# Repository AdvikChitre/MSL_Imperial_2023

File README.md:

# MSL_Imperial_2023
Repository for Imperial College London Robocup MSL team 2023

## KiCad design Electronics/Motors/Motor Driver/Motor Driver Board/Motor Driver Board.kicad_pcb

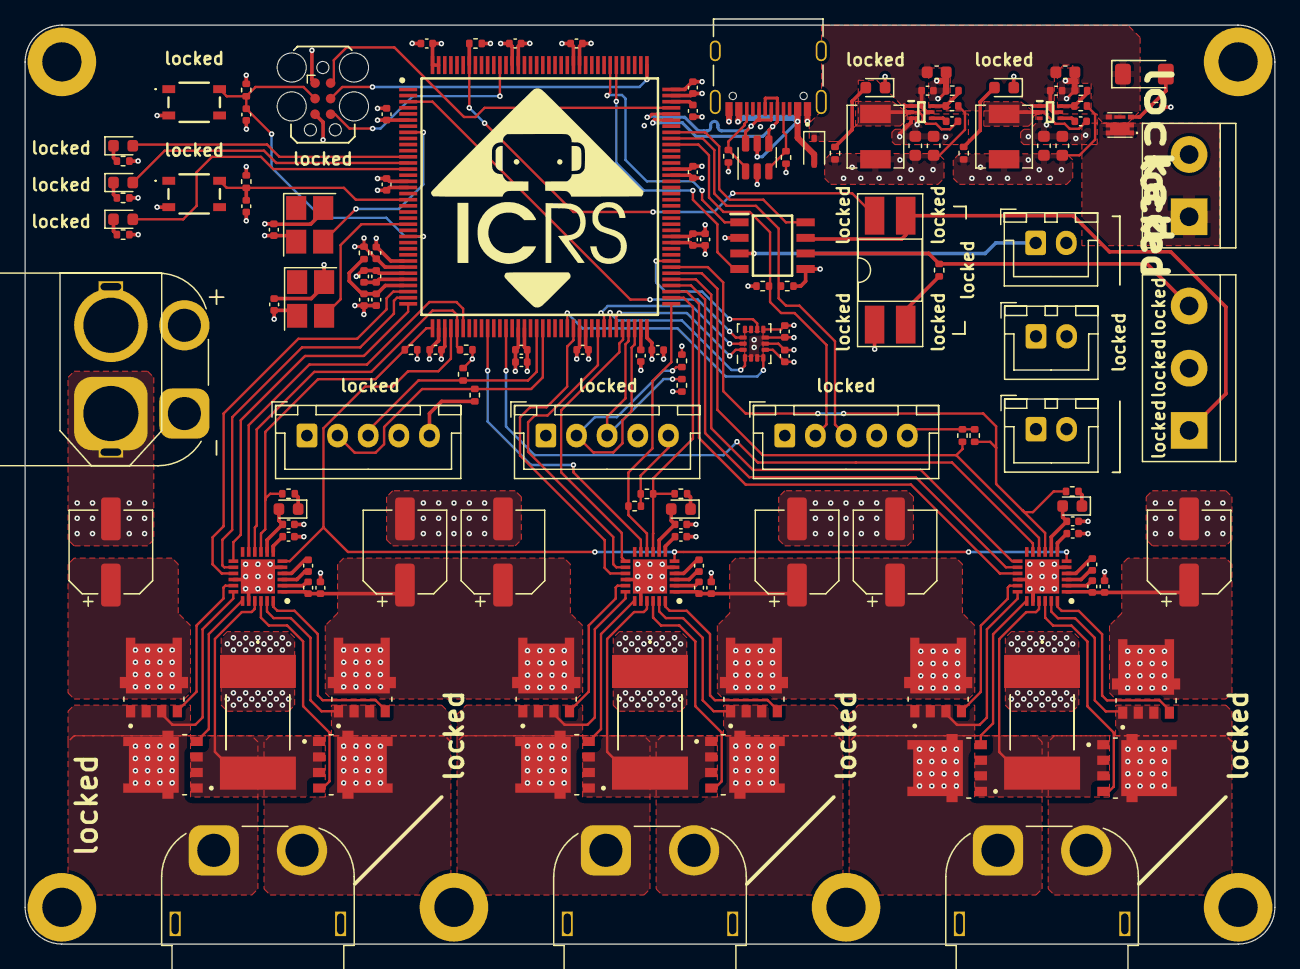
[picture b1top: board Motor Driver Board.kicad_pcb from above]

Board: 4 copper layers, 102.0 x 75.0 mm, 153 parts (0 on the bottom side), 114 nets.

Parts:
C201, C202, C207, C208, C209, C210: 22u; C_0603_1608Metric
C203, C204, C205, C206, C301, C302, C304, C306, C308, C309, C310, C312, C313, C314, C315, C317, C318, C319, C320, C322, C323, C326, C327, C405, C406, C411, C412, C415, C418: 100n; C_0402_1005Metric
C303, C328: 10n; C_0402_1005Metric
C307, C311, C401, C402, C403, C404, C407, C408, C413, C414, C416: 1u; C_0402_1005Metric
C316, C324: 10u; C_0402_1005Metric
C321, C325: 2u2; C_0402_1005Metric
C409, C410, C417, C419, C420, C421: 100u; CP_Elec_6.3x7.7
D201: ZMM10V; D_MiniMELF
D202, D203: GREEN; LED_0603_1608Metric
D301, D401, D402, D403: Red; LED_0603_1608Metric
D302: Green; LED_0603_1608Metric
D303: Blue; LED_0603_1608Metric
D304: BAT760-115; D_SOD-323
FB301: 120R@100MHz; R_0402_1005Metric
H101, H102, H103, H104, H105, H106: MountingHole_Pad; MountingHole_3.2mm_M3_DIN965_Pad
IC201, IC202: TPS563202DRLR; SOTFL50P160X60-6N
IC301: TJA1057GT/3; SOIC127P600X175-8N
IC302: STM32H723ZGT6; QFP50P2200X2200X160-144N
J201, J203, J204: JST-XH-2.50mm; JST_XH_B2B-XH-A_1x02_P2.50mm_Vertical
J202: Pluggable_Terminal_01x02; Pluggable_terminal-2_P5.08mm
J301: TC2030; Tag-Connect_TC2030-IDC-FP_2x03_P1.27mm_Vertical
J302: Pluggable_Terminal_01x03; Pluggable_terminal-3_P5.08mm
J303: TYPE-C-31-M-12; HRO_TYPE-C-31-M-12
J401, J402, J404: XT60PW-F; AMASS_XT60PW-F_1x02_P7.20mm_Horizontal
J403: XT60PW-M; AMASS_XT60PW-M_1x02_P7.20mm_Horizontal
J405: XT60-M-Vertical; AMASS_XT60-M_1x02_P7.20mm_Vertical
J406, J407, J409: JST_2.5mm_1x5; JST_XH_B5B-XH-A_1x05_P2.50mm_Vertical
L201: 4u7; L_Chilisin_BMRA00040420
L202: 3u3; L_Chilisin_BMRA00040420
Q201: DMP3028LFDE; DMP2066UFDE7
R201: 4k7; R_0402_1005Metric
R202: 52k; R_0402_1005Metric
R203, R205, R304, R308, R317, R403, R404, R405, R406, R410, R411: 10k; R_0402_1005Metric
R204: 31k; R_0402_1005Metric
R206, R311, R312, R313, R314, R315, R316: 2k2; R_0402_1005Metric
R207, R301, R302, R303, R401, R402, R409: 1k5; R_0402_1005Metric
R307: 120R; R_0402_1005Metric
R309, R310: 5k1; R_0402_1005Metric
R407, R408, R412: CSS2H-3920K-5L00F; CSS2H3920K5L00F
S301, S304: TS20-42-25-WT-160-SMT-TR; TS204225WT160SMTTRMSL
SW301: SW_DIP_x02; DIP-4_W8.89mm_SMDSocket_LongPads
T401, T402, T403, T404, T405, T406, T407, T408, T409, T410, T411, T412: NVMFS4C05NT1G; TRANS_NVMFS5834NLWFT1G
U302: LSM6DS3; LGA-14_3x2.5mm_P0.5mm_LayoutBorder3x4y
U303: USBLC6-4SC6-ES; SOT-23-6
U401, U402, U403: DRV8701ERGER; QFN50P400X400X100-25N-D
X301: 25MHz_Clock; Oscillator_SMD_Abracon_ASE-4Pin_3.2x2.5mm_HandSoldering
X302: 32.768kHz_Clock; Oscillator_SMD_Abracon_ASE-4Pin_3.2x2.5mm_HandSoldering

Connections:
+3.3V: C208.1, C210.1, C301.1, C302.2, C304.1, C308.1, C310.1, C312.1, C313.1, C314.1, C315.1, C316.1, C317.1, C318.1, C319.1, C320.1, C322.1, C323.1, C324.1, C326.1, C327.1, FB301.2, IC301.5 (VIO), IC302.6 (VBAT), IC302.17 (VDD_1), IC302.30 (VDD_2), IC302.39 (VDD_3), IC302.52 (VDD_4), IC302.62 (VDD_5), IC302.72 (VDD_6), IC302.84 (VDD_7), IC302.95 (VDD33USB), IC302.108 (VDD_8), IC302.121 (VDD_9), IC302.131 (VDD_10), IC302.143 (PDR_ON), IC302.144 (VDD_11), J301.1 (VCC), J406.5, J407.5, J409.5, L202.2, R204.1, R207.1, R304.2, R311.1, R312.1, R313.1, R314.1, R315.1, R316.1, R317.2, R403.1, R404.1, R405.1, R406.1, R410.1, R411.1, SW301.1, U302.5 (VDDIO), U302.8 (VDD), X301.4 (VDD), X302.4 (VDD)
+5V: C207.1, C209.1, IC301.3 (VCC), J201.1, J203.1, J204.1, L201.2, R202.1, R206.1
/Microcontroller/CANH: IC301.7 (CANH), J302.1, SW301.3
/Microcontroller/CANL: IC301.6 (CANL), J302.3, R307.1
/Microcontroller/CAN_SW: R307.2, SW301.2
/Microcontroller/CC1: J303.A5 (CC1), R309.1, U303.3 (IO2)
/Microcontroller/CC2: J303.B5 (CC2), R310.1, U303.1 (IO1)
/Microcontroller/LEDB_K: D303.1 (K), R303.2
/Microcontroller/LEDG_K: D302.1 (K), R302.2
/Microcontroller/LEDR_K: D301.1 (K), R301.2
/Microcontroller/VCAP1: C321.1, IC302.71 (VCAP_1)
/Microcontroller/VCAP2: C325.1, IC302.106 (VCAP_2)
/Microcontroller/VDDA: C309.1, C311.1, FB301.1, IC302.33 (VDDA)
/Microcontroller/VREF+: C306.1, C307.1, IC302.32 (VREF+)
/Motor Drivers/M1_AVDD: C402.1, U402.7 (AVDD)
/Motor Drivers/M1_CPH: C406.2, U402.3 (CPH)
/Motor Drivers/M1_CPL: C406.1, U402.4 (CPL)
/Motor Drivers/M1_DVDD: C404.1, D402.2 (A), U402.8 (DVDD)
/Motor Drivers/M1_GH1: T408.4 (G), U402.17 (GH1)
/Motor Drivers/M1_GH2: T405.4 (G), U402.24 (GH2)
/Motor Drivers/M1_GL1: T407.4 (G), U402.19 (GL1)
/Motor Drivers/M1_GL2: T406.4 (G), U402.22 (GL2)
/Motor Drivers/M1_NFAULT_K: D402.1 (K), R402.2
/Motor Drivers/M1_OUT_A: J402.2 (+), T405.1 (S), T405.2 (S), T405.3 (S), T406.5_6 (D), U402.23 (SH2)
/Motor Drivers/M1_OUT_B: J402.1 (-), T407.5_6 (D), T408.1 (S), T408.2 (S), T408.3 (S), U402.18 (SH1)
/Motor Drivers/M1_SP: R408.2, T406.1 (S), T406.2 (S), T406.3 (S), T407.1 (S), T407.2 (S), T407.3 (S), U402.21 (SP)
/Motor Drivers/M1_VCP: C408.2, U402.2 (VCP)
/Motor Drivers/M2_AVDD: C413.1, U403.7 (AVDD)
/Motor Drivers/M2_CPH: C415.2, U403.3 (CPH)
/Motor Drivers/M2_CPL: C415.1, U403.4 (CPL)
/Motor Drivers/M2_DVDD: C414.1, D403.2 (A), U403.8 (DVDD)
/Motor Drivers/M2_GH1: T412.4 (G), U403.17 (GH1)
/Motor Drivers/M2_GH2: T409.4 (G), U403.24 (GH2)
/Motor Drivers/M2_GL1: T411.4 (G), U403.19 (GL1)
/Motor Drivers/M2_GL2: T410.4 (G), U403.22 (GL2)
/Motor Drivers/M2_NFAULT_K: D403.1 (K), R409.2
/Motor Drivers/M2_OUT_A: J404.2 (+), T409.1 (S), T409.2 (S), T409.3 (S), T410.5_6 (D), U403.23 (SH2)
/Motor Drivers/M2_OUT_B: J404.1 (-), T411.5_6 (D), T412.1 (S), T412.2 (S), T412.3 (S), U403.18 (SH1)
/Motor Drivers/M2_SP: R412.2, T410.1 (S), T410.2 (S), T410.3 (S), T411.1 (S), T411.2 (S), T411.3 (S), U403.21 (SP)
/Motor Drivers/M2_VCP: C416.2, U403.2 (VCP)
/Motor Drivers/M3_AVDD: C401.1, U401.7 (AVDD)
/Motor Drivers/M3_CPH: C405.2, U401.3 (CPH)
/Motor Drivers/M3_CPL: C405.1, U401.4 (CPL)
/Motor Drivers/M3_DVDD: C403.1, D401.2 (A), U401.8 (DVDD)
/Motor Drivers/M3_GH1: T404.4 (G), U401.17 (GH1)
/Motor Drivers/M3_GH2: T401.4 (G), U401.24 (GH2)
/Motor Drivers/M3_GL1: T403.4 (G), U401.19 (GL1)
/Motor Drivers/M3_GL2: T402.4 (G), U401.22 (GL2)
/Motor Drivers/M3_NFAULT_K: D401.1 (K), R401.2
/Motor Drivers/M3_OUT_A: J401.2 (+), T401.1 (S), T401.2 (S), T401.3 (S), T402.5_6 (D), U401.23 (SH2)
/Motor Drivers/M3_OUT_B: J401.1 (-), T403.5_6 (D), T404.1 (S), T404.2 (S), T404.3 (S), U401.18 (SH1)
/Motor Drivers/M3_SP: R407.2, T402.1 (S), T402.2 (S), T402.3 (S), T403.1 (S), T403.2 (S), T403.3 (S), U401.21 (SP)
/Motor Drivers/M3_VCP: C407.2, U401.2 (VCP)
/Power/3V3_BST: C206.1, IC202.4 (BST)
/Power/3V3_FB: IC202.6 (FB), R204.2, R205.1
/Power/3V3_LED_A: D203.2 (A), R207.2
/Power/3V3_SW: C206.2, IC202.2 (SW), L202.1
/Power/5V_BST: C205.1, IC201.4 (BST)
/Power/5V_FB: IC201.6 (FB), R202.2, R203.1
/Power/5V_LED_A: D202.2 (A), R206.2
/Power/5V_SW: C205.2, IC201.2 (SW), L201.1
/Power/RP_PMOS_G: D201.2 (A), Q201.3 (G), R201.1
BOOT0: IC302.138 (BOOT0), R308.1, SW301.4
BTN: C303.1, IC302.19 (PF7), R304.1, S301.2 (NO_2)
CAN_RX: IC301.4 (RXD), IC302.114 (PD0)
CAN_TX: IC301.1 (TXD), IC302.115 (PD1)
CS: IC302.3 (PE4), U302.12 (CS)
GND: C201.2, C202.2, C203.2, C204.2, C207.2, C208.2, C209.2, C210.2, C301.2, C302.1, C303.2, C304.2, C306.2, C307.2, C308.2, C309.2, C310.2, C311.2, C312.2, C313.2, C314.2, C315.2, C316.2, C317.2, C318.2, C319.2, C320.2, C321.2, C322.2, C323.2, C324.2, C325.2, C326.2, C327.2, C328.2, C401.2, C402.2, C403.2, C404.2, C409.2, C410.2, C411.2, C412.2, C413.2, C414.2, C417.2, C418.2, C419.2, C420.2, C421.2, D202.1 (K), D203.1 (K), IC201.3 (GND), IC202.3 (GND), IC301.2 (GND), IC302.16 (VSS_1), IC302.29 (PC3_C), IC302.31 (VSSA), IC302.38 (VSS_2), IC302.51 (VSS_3), IC302.61 (VSS_4), IC302.83 (VSS_5), IC302.94 (VSS_6), IC302.107 (VSS_7), IC302.120 (VSS_8), IC302.130 (VSS_9), J201.2, J202.2, J203.2, J204.2, J301.5 (GND), J302.2, J303.A1_B12 (GND), J303.B1_A12 (GND), J403.1 (-), J403.SH1, J405.1 (-), J406.4, J407.4, J409.4, R201.2, R203.2, R205.2, R301.1, R302.1, R303.1, R308.2, R309.2, R310.2, R407.1, R408.1, R412.1, S301.3 (COM_1), S304.3 (COM_1), U302.2 (SDX), U302.3 (SCX), U302.6 (GND), U302.7 (GND), U303.2 (GND), U401.5 (GND_1), U401.16 (GND_2), U401.20 (SN), U401.25 (GND_3), U402.5 (GND_1), U402.16 (GND_2), U402.20 (SN), U402.25 (GND_3), U403.5 (GND_1), U403.16 (GND_2), U403.20 (SN), U403.25 (GND_3), X301.2 (GND), X302.2 (GND)
IMU_INT1: IC302.59 (PE8), U302.4 (INT1)
IMU_INT2: IC302.80 (PD11), U302.9 (INT2)
LEDB: D303.2 (A), IC302.14 (PF4)
LEDG: D302.2 (A), IC302.12 (PF2)
LEDR: D301.2 (A), IC302.13 (PF3)
M1_EN: IC302.35 (PA1), U402.14 (EN)
M1_NFAULT: IC302.37 (PA3), R402.1, R404.2, U402.9 (NFAULT)
M1_NSLEEP: IC302.36 (PA2), U402.13 (NSLEEP)
M1_PH: IC302.34 (PA0), U402.15 (PH)
M1_SNSOUT: IC302.41 (PA5), R406.2, U402.10 (SNSOUT)
M1_SO: IC302.42 (PA6), U402.11 (SO)
M2_EN: IC302.64 (PE11), U403.14 (EN)
M2_NFAULT: IC302.74 (PB13), R409.1, R410.2, U403.9 (NFAULT)
M2_NSLEEP: IC302.68 (PE15), U403.13 (NSLEEP)
M2_PH: IC302.60 (PE9), U403.15 (PH)
M2_SNSOUT: IC302.73 (PB12), R411.2, U403.10 (SNSOUT)
M2_SO: IC302.46 (PB0), U403.11 (SO)
M3_EN: IC302.76 (PB15), U401.14 (EN)
M3_NFAULT: IC302.79 (PD10), R401.1, R403.2, U401.9 (NFAULT)
M3_NSLEEP: IC302.77 (PD8), U401.13 (NSLEEP)
M3_PH: IC302.75 (PB14), U401.15 (PH)
M3_SNSOUT: IC302.78 (PD9), R405.2, U401.10 (SNSOUT)
M3_SO: IC302.49 (PF11), U401.11 (SO)
MISO: IC302.66 (PE13), U302.1 (SDO/SA0)
MOSI: IC302.67 (PE14), U302.14 (SDA)
NRST: C328.1, IC302.25 (NRST), J301.3 (~RESET), R317.1, S304.2 (NO_2)
OSC25M: IC302.23 (PH0-OSC_IN), X301.3 (OUT)
OSC32K: IC302.8 (PC14-OSC32_IN), X302.3 (OUT)
SCK: IC302.65 (PE12), U302.13 (SCL)
SCL2: IC302.69 (PB10), J406.3, R315.2
SCL3: IC302.100 (PA8), J407.3, R311.2
SCL4: IC302.54 (PF14), J409.3, R312.2
SDA2: IC302.70 (PB11), J406.2, R316.2
SDA3: IC302.99 (PC9), J407.2, R313.2
SDA4: IC302.55 (PF15), J409.2, R314.2
SILENT: IC301.8 (S), IC302.101 (PA9)
SWCLK: IC302.109 (PA14), J301.4 (SWCLK)
SWDIO: IC302.105 (PA13), J301.2 (SWDIO)
SWO: IC302.133 (PB3), J301.6 (SWO)
USB_DN: IC302.103 (PA11), J303.A7 (DN1), J303.B7 (DN2), U303.4 (IO3)
USB_DP: IC302.104 (PA12), J303.A6 (DP1), J303.B6 (DP2), U303.6 (IO4)
VBUS: D304.2 (A), J303.A4_B9 (VBUS), J303.B4_A9 (VBUS), U303.5 (VBUS)
VIN: C201.1, C202.1, C203.1, C204.1, D201.1 (K), D304.1 (K), IC201.1 (VIN), IC201.5 (EN), IC202.1 (VIN), IC202.5 (EN), Q201.4 (S_1), Q201.7 (S_2)
VIN_RAW: J202.1, Q201.1 (D_1), Q201.2 (D_2), Q201.5 (D_3), Q201.6 (D_4), Q201.8 (D_5)
VMOT: C407.1, C408.1, C409.1, C410.1, C411.1, C412.1, C416.1, C417.1, C418.1, C419.1, C420.1, C421.1, J403.2 (+), J403.SH2, J405.2 (+), T401.5_6 (D), T404.5_6 (D), T405.5_6 (D), T408.5_6 (D), T409.5_6 (D), T412.5_6 (D), U401.1 (VM), U402.1 (VM), U403.1 (VM)
VREF: IC302.40 (PA4), U401.6 (VREF), U402.6 (VREF), U403.6 (VREF)

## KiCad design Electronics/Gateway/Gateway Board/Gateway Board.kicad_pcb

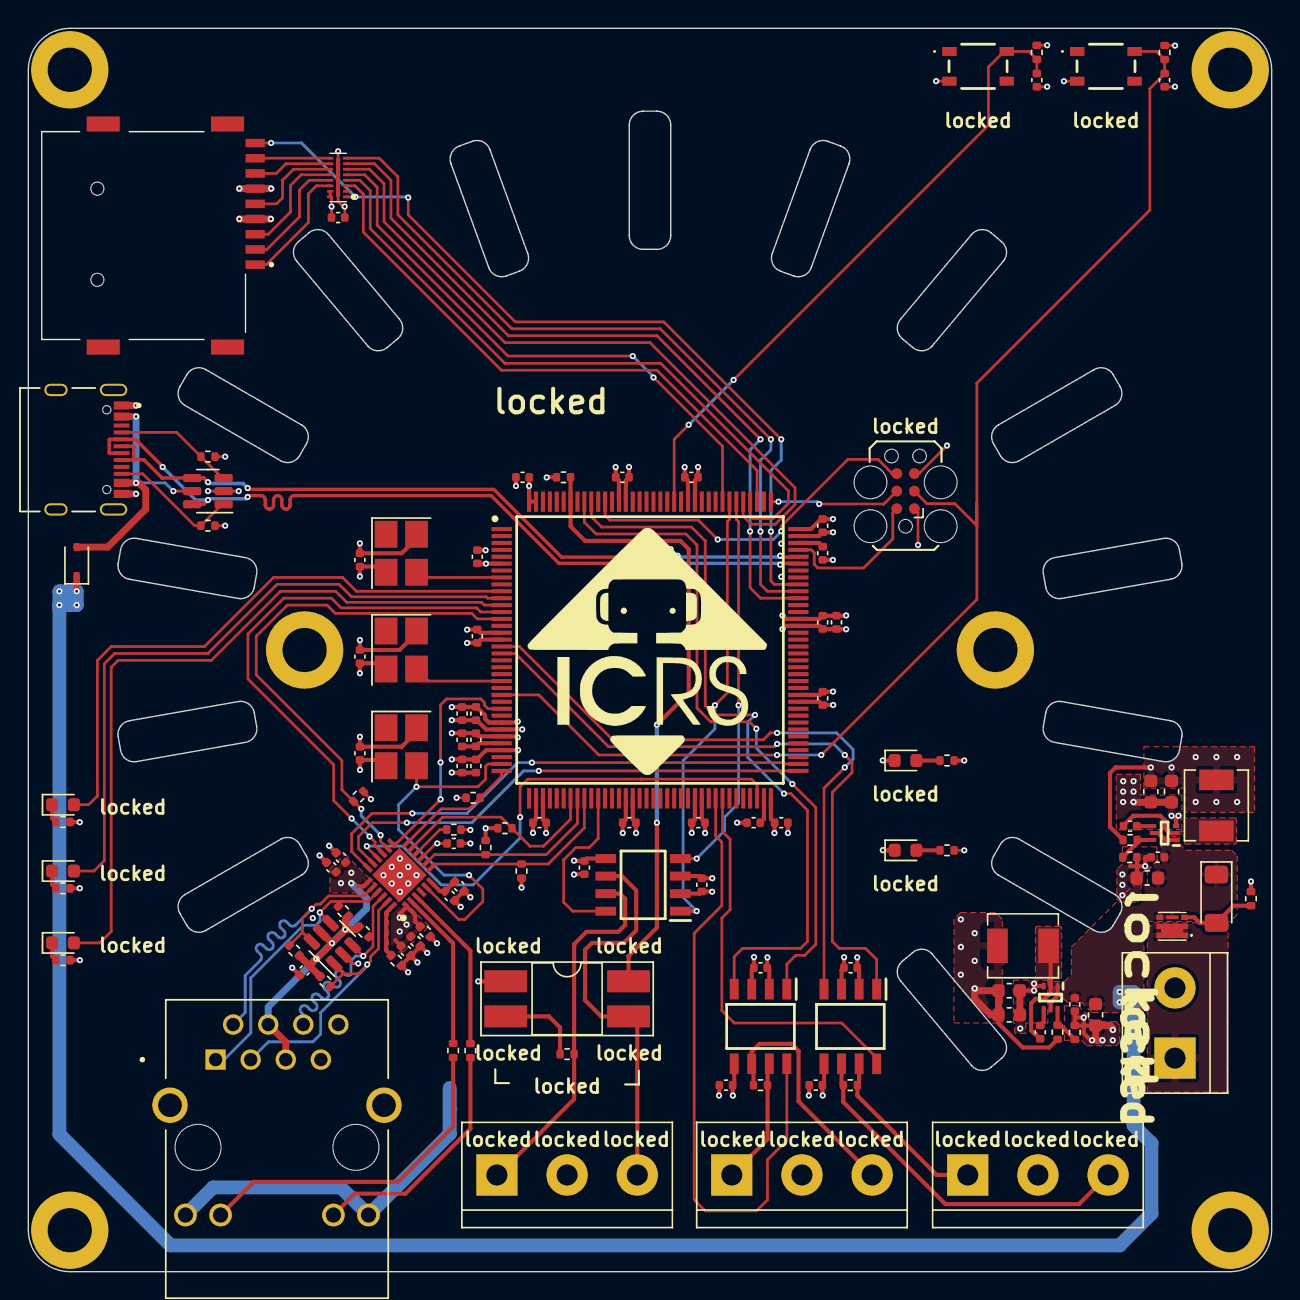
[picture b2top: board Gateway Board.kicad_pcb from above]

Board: 4 copper layers, 90.0 x 90.0 mm, 123 parts (0 on the bottom side), 88 nets.

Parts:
C1, C2, C3, C4, C5, C6, C203, C204, C205, C206, C301, C302, C303, C305, C307, C308, C309, C311, C312, C313, C314, C316, C317, C318, C319, C320, C321, C327, C401, C404, C405, C406, C408: 100n; C_0402_1005Metric
C201, C202, C207, C208, C209, C210: 22u; C_0603_1608Metric
C304, C326: 10n; C_0402_1005Metric
C306, C310, C402: 1u; C_0402_1005Metric
C315, C322, C325, C407: 10u; C_0402_1005Metric
C323, C324: 2u2; C_0402_1005Metric
C403: 470p; C_0402_1005Metric
D201, D202: GREEN; LED_0603_1608Metric
D204: ZMM10V; D_MiniMELF
D301: Red; LED_0603_1608Metric
D302: Green; LED_0603_1608Metric
D303: Blue; LED_0603_1608Metric
D304: BAT760-115; D_SOD-323
FB401: 120R@100MHz; R_0402_1005Metric
FL301: EMIF06-MSD02N16; EMIF06MSD02N16
H101, H102, H103, H104, H105, H106: MountingHole_Pad; MountingHole_3.2mm_M3_DIN965_Pad
IC201, IC202: TPS563202DRLR; SOTFL50P160X60-6N
IC301: STM32H723ZGT6; QFP50P2200X2200X160-144N
IC302, IC303, IC304: TJA1057GT/3; SOIC127P600X175-8N
IC401: LAN8742A-CZ-TR; QFN50P400X400X100-25N-D
J201: Pluggable_Terminal_01x02; Pluggable_terminal-2_P5.08mm
J301: TC2030; Tag-Connect_TC2030-IDC-FP_2x03_P1.27mm_Vertical
J302: MEM2075-00-140-01-A; MEM20750014001A
J303: TYPE-C-31-M-12; HRO_TYPE-C-31-M-12
J304, J305, J306: Pluggable_Terminal_01x03; Pluggable_terminal-3_P5.08mm
J401: HR913129A; HANRUN_HR913129A
L201: 4u7; L_Chilisin_BMRA00040420
L202: 3u3; L_Chilisin_BMRA00040420
Q201: DMP3028LFDE; DMP2066UFDE7
R201: 52k; R_0402_1005Metric
R202, R204, R305, R306, R311, R401, R402, R403, R404, R406: 10k; R_0402_1005Metric
R203: 31k; R_0402_1005Metric
R205: 2k2; R_0402_1005Metric
R206, R301, R303, R304, R405: 1k5; R_0402_1005Metric
R207: 4k7; R_0402_1005Metric
R302, R307, R310: 120R; R_0402_1005Metric
R308, R309: 5k1; R_0402_1005Metric
R407: 12k1; R_0402_1005Metric
R408, R409, R410, R411: 49R9; R_0402_1005Metric
R412, R413: 330R; R_0402_1005Metric
S301, S302: TS20-42-25-WT-160-SMT-TR; TS204225WT160SMTTRMSL
SW301: SW_DIP_x02; DIP-4_W8.89mm_SMDSocket_LongPads
U302, U401: USBLC6-4SC6-ES; SOT-23-6
X301: 50MHz_Clock; Oscillator_SMD_Abracon_ASE-4Pin_3.2x2.5mm_HandSoldering
X302: 25MHz_Clock; Oscillator_SMD_Abracon_ASE-4Pin_3.2x2.5mm_HandSoldering
X303: 32.768kHz_Clock; Oscillator_SMD_Abracon_ASE-4Pin_3.2x2.5mm_HandSoldering

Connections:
+3.3V: C1.1, C3.1, C5.1, C208.1, C210.1, C301.2, C302.2, C303.2, C307.1, C308.1, C309.1, C310.1, C311.1, C312.1, C313.1, C314.1, C315.1, C316.1, C317.1, C318.1, C319.1, C320.1, C321.1, C322.1, C325.1, C327.1, C401.2, FB401.2, FL301.15 (VCC), FL301.16 (RDATA_VCC), IC301.6 (VBAT), IC301.17 (VDD_1), IC301.30 (VDD_2), IC301.33 (VDDA), IC301.39 (VDD_3), IC301.52 (VDD_4), IC301.62 (VDD_5), IC301.72 (VDD_6), IC301.84 (VDD_7), IC301.95 (VDD33USB), IC301.108 (VDD_8), IC301.121 (VDD_9), IC301.131 (VDD_10), IC301.143 (PDR_ON), IC301.144 (VDD_11), IC302.5 (VIO), IC303.5 (VIO), IC304.5 (VIO), IC401.9 (VDDIO), J301.1 (VCC), J302.4 (VDD), J401.9, J401.12, L202.2, R203.1, R206.1, R305.2, R311.2, R402.1, R403.1, R404.1, R405.1, R406.1, SW301.1, X301.4 (VDD), X302.4 (VDD), X303.4 (VDD)
+3.3VA: C404.1, C405.1, C406.1, C407.1, C408.1, FB401.1, IC401.1 (VDD2A), IC401.19 (VDD1A), J401.4 (TCT), J401.5 (RCT), R408.1, R409.1, R410.1, R411.1, U401.5 (VBUS)
+5V: C2.1, C4.1, C6.1, C207.1, C209.1, IC302.3 (VCC), IC303.3 (VCC), IC304.3 (VCC), L201.2, R201.1, R205.1
/Ethernet/G_K: J401.10, R412.2
/Ethernet/LED1: IC401.3 (LED1/REGOFF), R413.1
/Ethernet/LED2: IC401.2 (LED2/~INTSEL), R412.1
/Ethernet/PHYAD0: IC401.10 (RXER/PHYAD0), R401.1
/Ethernet/RBIAS: IC401.24 (RBIAS), R407.1
/Ethernet/RXN: IC401.22 (RXN), J401.6 (RD-), R411.2, U401.3 (IO2)
/Ethernet/RXP: IC401.23 (RXP), J401.3 (RD+), R410.2, U401.1 (IO1)
/Ethernet/TXN: IC401.20 (TXN), J401.2 (TD-), R409.2, U401.6 (IO4)
/Ethernet/TXP: IC401.21 (TXP), J401.1 (TD+), R408.2, U401.4 (IO3)
/Ethernet/VDDCR: C402.1, C403.1, IC401.6 (VDDCR)
/Ethernet/Y_K: J401.11, R413.2
/Microcontroller/CANH1: IC302.7 (CANH), J304.1, R302.1
/Microcontroller/CANH2: IC303.7 (CANH), J305.1, R307.2
/Microcontroller/CANH3: IC304.7 (CANH), J306.1, R310.2
/Microcontroller/CANL1: IC302.6 (CANL), J304.3, SW301.3
/Microcontroller/CANL2: IC303.6 (CANL), J305.3, R307.1
/Microcontroller/CANL3: IC304.6 (CANL), J306.3, R310.1
/Microcontroller/CAN_SW: R302.2, SW301.2
/Microcontroller/CC1: J303.A5 (CC1), R308.1, U302.3 (IO2)
/Microcontroller/CC2: J303.B5 (CC2), R309.1, U302.1 (IO1)
/Microcontroller/CLK: FL301.11 (CLK_EX), J302.5 (CLK)
/Microcontroller/CMD: FL301.12 (CMD_EX), J302.3 (CMD)
/Microcontroller/DAT0: FL301.10 (DAT0_EX), J302.7 (DAT0)
/Microcontroller/DAT1: FL301.9 (DAT1_EX), J302.8 (DAT1)
/Microcontroller/DAT2: FL301.14 (DAT2_EX), J302.1 (DAT2)
/Microcontroller/DAT3: FL301.13 (DAT3_EX), J302.2 (CD/DAT3)
/Microcontroller/LEDB_K: D303.1 (K), R304.2
/Microcontroller/LEDG_K: D302.1 (K), R303.2
/Microcontroller/LEDR_K: D301.1 (K), R301.2
/Microcontroller/VCAP1: C323.1, IC301.71 (VCAP_1)
/Microcontroller/VCAP2: C324.1, IC301.106 (VCAP_2)
/Microcontroller/VREF+: C305.1, C306.1, IC301.32 (VREF+)
/Power/3V3_BST: C206.1, IC202.4 (BST)
/Power/3V3_FB: IC202.6 (FB), R203.2, R204.1
/Power/3V3_LED_A: D202.2 (A), R206.2
/Power/3V3_SW: C206.2, IC202.2 (SW), L202.1
/Power/5V_BST: C205.1, IC201.4 (BST)
/Power/5V_FB: IC201.6 (FB), R201.2, R202.1
/Power/5V_LED_A: D201.2 (A), R205.2
/Power/5V_SW: C205.2, IC201.2 (SW), L201.1
/Power/RP_PMOS_G: D204.2 (A), Q201.3 (G), R207.1
BOOT0: IC301.138 (BOOT0), R306.1, SW301.4
BTN: C326.1, IC301.123 (PD7), R311.1, S302.2 (NO_2)
CAN_RX1: IC301.114 (PD0), IC302.4 (RXD)
CAN_RX2: IC301.135 (PB5), IC303.4 (RXD)
CAN_RX3: IC301.18 (PF6), IC304.4 (RXD)
CAN_TX1: IC301.115 (PD1), IC302.1 (TXD)
CAN_TX2: IC301.136 (PB6), IC303.1 (TXD)
CAN_TX3: IC301.19 (PF7), IC304.1 (TXD)
ETH_CRS_DV: IC301.43 (PA7), IC401.11 (CRS_DV/MODE2), R404.2
ETH_INT: IC301.14 (PF4), IC401.14 (~INT/REFCLKO), R406.2
ETH_MDC: IC301.27 (PC1), IC401.13 (MDC)
ETH_MDIO: IC301.36 (PA2), IC401.12 (MDIO), R405.2
ETH_REF_CLK: IC301.35 (PA1), IC401.5 (XTAL1/CLKIN), X301.3 (OUT)
ETH_RST: IC301.13 (PF3), IC401.15 (~RST)
ETH_RXD0: IC301.44 (PC4), IC401.8 (RXD0/MODE0), R402.2
ETH_RXD1: IC301.45 (PC5), IC401.7 (RXD1/MODE1), R403.2
ETH_TXD0: IC301.73 (PB12), IC401.17 (TXD0)
ETH_TXD1: IC301.74 (PB13), IC401.18 (TXD1)
ETH_TX_EN: IC301.70 (PB11), IC401.16 (TXEN)
GND: C1.2, C2.2, C3.2, C4.2, C5.2, C6.2, C201.2, C202.2, C203.2, C204.2, C207.2, C208.2, C209.2, C210.2, C301.1, C302.1, C303.1, C304.2, C305.2, C306.2, C307.2, C308.2, C309.2, C310.2, C311.2, C312.2, C313.2, C314.2, C315.2, C316.2, C317.2, C318.2, C319.2, C320.2, C321.2, C322.2, C323.2, C324.2, C325.2, C326.2, C327.2, C401.1, C402.2, C403.2, C404.2, C405.2, C406.2, C407.2, C408.2, D201.1 (K), D202.1 (K), FL301.17 (EP_(GND)), IC201.3 (GND), IC202.3 (GND), IC301.16 (VSS_1), IC301.29 (PC3_C), IC301.31 (VSSA), IC301.38 (VSS_2), IC301.51 (VSS_3), IC301.61 (VSS_4), IC301.83 (VSS_5), IC301.94 (VSS_6), IC301.107 (VSS_7), IC301.120 (VSS_8), IC301.130 (VSS_9), IC302.2 (GND), IC303.2 (GND), IC304.2 (GND), IC401.25 (VSS), J201.2, J301.5 (GND), J302.6 (VSS), J303.A1_B12 (GND), J303.B1_A12 (GND), J304.2, J305.2, J306.2, J401.8 (CHS_GND), J401.S1 (SHIELD), J401.S2 (SHIELD), R202.2, R204.2, R207.2, R301.1, R303.1, R304.1, R306.2, R308.2, R309.2, R401.2, R407.2, S301.3 (COM_1), S302.3 (COM_1), U302.2 (GND), U401.2 (GND), X301.2 (GND), X302.2 (GND), X303.2 (GND)
LEDB: D303.2 (A), IC301.12 (PF2)
LEDG: D302.2 (A), IC301.10 (PF0)
LEDR: D301.2 (A), IC301.11 (PF1)
NRST: C304.1, IC301.25 (NRST), J301.3 (~RESET), R305.1, S301.2 (NO_2)
OSC25M: IC301.23 (PH0-OSC_IN), X302.3 (OUT)
OSC32K: IC301.8 (PC14-OSC32_IN), X303.3 (OUT)
SDMMC1_CD: FL301.1 (WP/CD), IC301.100 (PA8), J302.9 (CD)
SDMMC1_CLK: FL301.6 (CLK_IN), IC301.113 (PC12)
SDMMC1_CMD: FL301.5 (CMD_IN), IC301.116 (PD2)
SDMMC1_DAT0: FL301.7 (DAT0_IN), IC301.98 (PC8)
SDMMC1_DAT1: FL301.8 (DAT1_IN), IC301.99 (PC9)
SDMMC1_DAT2: FL301.3 (DAT2_IN), IC301.111 (PC10)
SDMMC1_DAT3: FL301.4 (DAT3_IN), IC301.112 (PC11)
SILENT1: IC301.47 (PB1), IC302.8 (S)
SILENT2: IC301.64 (PE11), IC303.8 (S)
SILENT3: IC301.65 (PE12), IC304.8 (S)
SWCLK: IC301.109 (PA14), J301.4 (SWCLK)
SWDIO: IC301.105 (PA13), J301.2 (SWDIO)
SWO: IC301.133 (PB3), J301.6 (SWO)
USB_DN: IC301.103 (PA11), J303.A7 (DN1), J303.B7 (DN2), U302.6 (IO4)
USB_DP: IC301.104 (PA12), J303.A6 (DP1), J303.B6 (DP2), U302.4 (IO3)
VBUS: D304.2 (A), J303.A4_B9 (VBUS), J303.B4_A9 (VBUS), U302.5 (VBUS)
VIN: C201.1, C202.1, C203.1, C204.1, D204.1 (K), D304.1 (K), IC201.1 (VIN), IC201.5 (EN), IC202.1 (VIN), IC202.5 (EN), Q201.4 (S_1), Q201.7 (S_2)
VIN_RAW: J201.1, Q201.1 (D_1), Q201.2 (D_2), Q201.5 (D_3), Q201.6 (D_4), Q201.8 (D_5)

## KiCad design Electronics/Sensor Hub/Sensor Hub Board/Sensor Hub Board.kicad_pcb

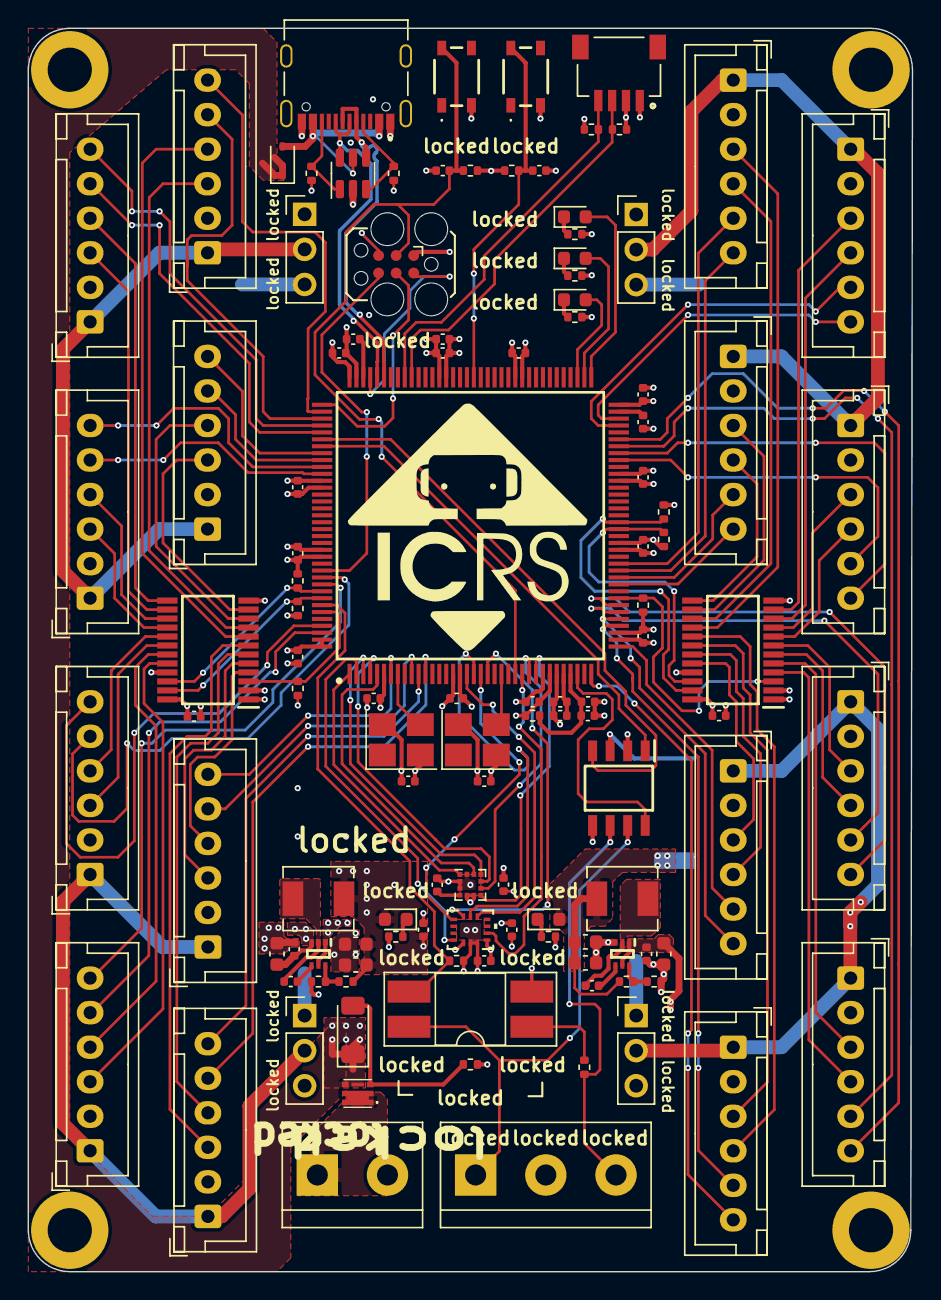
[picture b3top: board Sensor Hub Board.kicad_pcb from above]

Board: 4 copper layers, 64.0 x 90.0 mm, 119 parts (0 on the bottom side), 132 nets.

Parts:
C201, C202, C207, C208, C209, C210: 22u; C_0603_1608Metric
C203, C204, C205, C206, C301, C302, C304, C306, C307, C308, C310, C311, C312, C313, C315, C316, C317, C318, C320, C321, C401, C402, C403, C404, C405, C407: 100n; C_0402_1005Metric
C303, C324: 10n; C_0402_1005Metric
C305, C309, C406: 1u; C_0402_1005Metric
C314, C322: 10u; C_0402_1005Metric
C319, C323: 2u2; C_0402_1005Metric
D201: ZMM10V; D_MiniMELF
D202, D203: GREEN; LED_0603_1608Metric
D301: Red; LED_0603_1608Metric
D302: Green; LED_0603_1608Metric
D303: Blue; LED_0603_1608Metric
D304: BAT760-115; D_SOD-323
FB301: 120R@100MHz; R_0402_1005Metric
H101, H102, H103, H104: MountingHole_Pad; MountingHole_3.2mm_M3_DIN965_Pad
IC201, IC202: TPS563202DRLR; SOTFL50P160X60-6N
IC301: TJA1057GT/3; SOIC127P600X175-8N
IC302: STM32H723ZGT6; QFP50P2200X2200X160-144N
J203: Pluggable_Terminal_01x02; Pluggable_terminal-2_P5.08mm
J301: TC2030; Tag-Connect_TC2030-IDC-FP_2x03_P1.27mm_Vertical
J302: Pluggable_Terminal_01x03; Pluggable_terminal-3_P5.08mm
J303: TYPE-C-31-M-12; HRO_TYPE-C-31-M-12
J304: JST_SH_1mm_1x4
J401, J402, J403, J404, J405, J406, J407, J408, J409, J410, J411, J412, J413, J414, J415, J416: JST_2.5mm_1x6; JST_XH_B6B-XH-A_1x06_P2.50mm_Vertical
JP401, JP402, JP403, JP404: Jumper_3_Bridged12; PinHeader_1x03_P2.54mm_Vertical
L201: 4u7; L_Chilisin_BMRA00040420
L202: 3u3; L_Chilisin_BMRA00040420
Q201: DMP3028LFDE; DMP2066UFDE7
R201: 4k7; R_0402_1005Metric
R202: 52k; R_0402_1005Metric
R203, R205, R304, R306, R313, R401, R402: 10k; R_0402_1005Metric
R204: 31k; R_0402_1005Metric
R206, R309, R310, R311, R312, R314, R315: 2k2; R_0402_1005Metric
R207, R301, R302, R303: 1k5; R_0402_1005Metric
R305: 120R; R_0402_1005Metric
R307, R308: 5k1; R_0402_1005Metric
S301, S302: TS20-42-25-WT-160-SMT-TR; TS204225WT160SMTTRMSL
SW301: SW_DIP_x02; DIP-4_W8.89mm_SMDSocket_LongPads
U302: USBLC6-4SC6-ES; SOT-23-6
U401, U403: TCA9548APWR; SOP65P640X120-24N
U402: BMI270; BMI270_BOS
U404: LIS3MDL; LGA-12_2x2mm_P0.5mm
X301: 25MHz_Clock; Oscillator_SMD_Abracon_ASE-4Pin_3.2x2.5mm_HandSoldering
X302: 32.768kHz_Clock; Oscillator_SMD_Abracon_ASE-4Pin_3.2x2.5mm_HandSoldering

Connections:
+3.3V: C208.1, C210.1, C301.1, C302.2, C306.1, C308.1, C310.1, C311.1, C312.1, C313.1, C314.1, C315.1, C316.1, C317.1, C318.1, C320.1, C321.1, C322.1, C401.1, C402.1, C403.1, C404.1, C405.1, C406.1, D203.2 (A), FB301.2, IC301.5 (VIO), IC302.6 (VBAT), IC302.17 (VDD_1), IC302.30 (VDD_2), IC302.39 (VDD_3), IC302.52 (VDD_4), IC302.62 (VDD_5), IC302.72 (VDD_6), IC302.84 (VDD_7), IC302.95 (VDD33USB), IC302.108 (VDD_8), IC302.121 (VDD_9), IC302.131 (VDD_10), IC302.143 (PDR_ON), IC302.144 (VDD_11), J301.1 (VCC), J304.2, JP401.1 (A), JP402.1 (A), JP403.1 (A), JP404.1 (A), L202.2, R204.1, R304.2, R309.1, R310.1, R311.1, R312.1, R313.2, R314.1, R315.1, R401.2, R402.2, SW301.2, U401.24 (VCC), U402.5 (VDDIO), U402.8 (VDD), U403.24 (VCC), U404.5 (Vdd), U404.6 (Vdd_IO), X301.4 (VDD), X302.4 (VDD)
+5V: C207.1, C209.1, D202.2 (A), IC301.3 (VCC), JP401.3 (B), JP402.3 (B), JP403.3 (B), JP404.3 (B), L201.2, R202.1
/Microcontroller/CANH: IC301.7 (CANH), J302.1, SW301.4
/Microcontroller/CANL: IC301.6 (CANL), J302.3, R305.1
/Microcontroller/CAN_SW: R305.2, SW301.1
/Microcontroller/CC1: J303.A5 (CC1), R307.1, U302.3 (IO2)
/Microcontroller/CC2: J303.B5 (CC2), R308.1, U302.1 (IO1)
/Microcontroller/LEDB_K: D303.1 (K), R303.2
/Microcontroller/LEDG_K: D302.1 (K), R302.2
/Microcontroller/LEDR_K: D301.1 (K), R301.2
/Microcontroller/VCAP1: C319.1, IC302.71 (VCAP_1)
/Microcontroller/VCAP2: C323.1, IC302.106 (VCAP_2)
/Microcontroller/VDDA: C307.1, C309.1, FB301.1, IC302.33 (VDDA)
/Microcontroller/VREF+: C304.1, C305.1, IC302.32 (VREF+)
/Power/3V3_BST: C206.1, IC202.4 (BST)
/Power/3V3_FB: IC202.6 (FB), R204.2, R205.1
/Power/3V3_LED_K: D203.1 (K), R207.1
/Power/3V3_SW: C206.2, IC202.2 (SW), L202.1
/Power/5V_BST: C205.1, IC201.4 (BST)
/Power/5V_FB: IC201.6 (FB), R202.2, R203.1
/Power/5V_LED_K: D202.1 (K), R206.1
/Power/5V_SW: C205.2, IC201.2 (SW), L201.1
/Power/RP_PMOS_G: D201.2 (A), Q201.3 (G), R201.1
/Sensors & connectors/MAG_C1: C407.1, U404.4 (C1)
BOOT0: IC302.138 (BOOT0), R306.1, SW301.3
BTN: C324.1, IC302.90 (PG5), R313.1, S302.2 (NO_2)
CAN_RX: IC301.4 (RXD), IC302.114 (PD0)
CAN_TX: IC301.1 (TXD), IC302.115 (PD1)
GND: C201.2, C202.2, C203.2, C204.2, C207.2, C208.2, C209.2, C210.2, C301.2, C302.1, C303.2, C304.2, C305.2, C306.2, C307.2, C308.2, C309.2, C310.2, C311.2, C312.2, C313.2, C314.2, C315.2, C316.2, C317.2, C318.2, C319.2, C320.2, C321.2, C322.2, C323.2, C324.2, C401.2, C402.2, C403.2, C404.2, C405.2, C406.2, C407.2, IC201.3 (GND), IC202.3 (GND), IC301.2 (GND), IC302.16 (VSS_1), IC302.29 (PC3_C), IC302.31 (VSSA), IC302.38 (VSS_2), IC302.51 (VSS_3), IC302.61 (VSS_4), IC302.83 (VSS_5), IC302.94 (VSS_6), IC302.107 (VSS_7), IC302.120 (VSS_8), IC302.130 (VSS_9), J203.2, J301.5 (GND), J302.2, J303.A1_B12 (GND), J303.B1_A12 (GND), J304.1, J401.2, J402.2, J403.2, J404.2, J405.2, J406.2, J407.2, J408.2, J409.2, J410.2, J411.2, J412.2, J413.2, J414.2, J415.2, J416.2, R201.2, R203.2, R205.2, R206.2, R207.2, R301.1, R302.1, R303.1, R306.2, R307.2, R308.2, S301.3 (COM_1), S302.3 (COM_1), U302.2 (GND), U401.1 (A0), U401.2 (A1), U401.12 (GND), U401.21 (A2), U402.6 (GNDIO), U402.7 (GND), U403.1 (A0), U403.2 (A1), U403.12 (GND), U403.21 (A2), U404.2 (GND), U404.3 (GND), U404.12 (GND), X301.2 (GND), X302.2 (GND)
GPIO0A: IC302.40 (PA4), J401.5
GPIO0B: IC302.36 (PA2), J401.6
GPIO1A: IC302.37 (PA3), J405.5
GPIO1B: IC302.41 (PA5), J405.6
GPIO2A: IC302.66 (PE13), J402.5
GPIO2B: IC302.67 (PE14), J402.6
GPIO3A: IC302.42 (PA6), J406.5
GPIO3B: IC302.43 (PA7), J406.6
GPIO4A: IC302.64 (PE11), J409.5
GPIO4B: IC302.65 (PE12), J409.6
GPIO5A: IC302.69 (PB10), J413.5
GPIO5B: IC302.70 (PB11), J413.6
GPIO6A: IC302.49 (PF11), J410.5
GPIO6B: IC302.48 (PB2), J410.6
GPIO7A: IC302.47 (PB1), J414.5
GPIO7B: IC302.46 (PB0), J414.6
GPIO8A: IC302.12 (PF2), J403.5
GPIO8B: IC302.11 (PF1), J403.6
GPIO9A: IC302.10 (PF0), J407.5
GPIO9B: IC302.7 (PC13), J407.6
GPIO10A: IC302.142 (PE1), J404.5
GPIO10B: IC302.135 (PB5), J404.6
GPIO11A: IC302.134 (PB4), J408.5
GPIO11B: IC302.141 (PE0), J408.6
GPIO12A: IC302.119 (PD5), J411.5
GPIO12B: IC302.118 (PD4), J411.6
GPIO13A: IC302.117 (PD3), J415.5
GPIO13B: IC302.116 (PD2), J415.6
GPIO14A: IC302.113 (PC12), J412.5
GPIO14B: IC302.112 (PC11), J412.6
GPIO15A: IC302.111 (PC10), J416.5
GPIO15B: IC302.110 (PA15), J416.6
IMU_CS: IC302.18 (PF6), U402.12 (CSB)
IMU_INT1: IC302.2 (PE3), U402.4 (INT1)
IMU_INT2: IC302.26 (PC0), U402.9 (INT2)
IMU_MISO: IC302.20 (PF8), U402.1 (SDO)
IMU_MOSI: IC302.21 (PF9), U402.14 (SDX)
IMU_SCK: IC302.19 (PF7), U402.13 (SCX)
LEDB: D303.2 (A), IC302.75 (PB14)
LEDG: D302.2 (A), IC302.73 (PB12)
LEDR: D301.2 (A), IC302.74 (PB13)
MAG_CS: IC302.3 (PE4), U404.10 (~CS)
MAG_DRDY: IC302.27 (PC1), U404.8 (DRDY)
MAG_INT: IC302.28 (PC2_C), U404.7 (INT)
MAG_MISO: IC302.4 (PE5), U404.9 (SDO/SA1)
MAG_MOSI: IC302.5 (PE6), U404.11 (SDA/SDI/SDO)
MAG_SCK: IC302.1 (PE2), U404.1 (SCL/SPC)
MUX1_RST: IC302.139 (PB8), R402.1, U403.3 (~RESET)
MUX2_RST: IC302.44 (PC4), R401.1, U401.3 (~RESET)
NRST: C303.1, IC302.25 (NRST), J301.3 (~RESET), R304.1, S301.2 (NO_2)
OSC25M: IC302.23 (PH0-OSC_IN), X301.3 (OUT)
OSC32K: IC302.8 (PC14-OSC32_IN), X302.3 (OUT)
SCL0: J401.3, U401.18 (SC6)
SCL1: J405.3, U401.20 (SC7)
SCL1_MCU: IC302.136 (PB6), R309.2, U403.22 (SCL)
SCL2: J402.3, U401.5 (SC0)
SCL3: J406.3, U401.7 (SC1)
SCL3_MCU: IC302.100 (PA8), J304.4, R311.2
SCL4: J409.3, U401.9 (SC2)
SCL4_MCU: IC302.54 (PF14), R314.2, U401.22 (SCL)
SCL5: J413.3, U401.11 (SC3)
SCL6: J410.3, U401.16 (SC5)
SCL7: J414.3, U401.14 (SC4)
SCL8: J403.3, U403.7 (SC1)
SCL9: J407.3, U403.5 (SC0)
SCL10: J404.3, U403.20 (SC7)
SCL11: J408.3, U403.18 (SC6)
SCL12: J411.3, U403.16 (SC5)
SCL13: J415.3, U403.11 (SC3)
SCL14: J412.3, U403.14 (SC4)
SCL15: J416.3, U403.9 (SC2)
SDA0: J401.4, U401.17 (SD6)
SDA1: J405.4, U401.19 (SD7)
SDA1_MCU: IC302.137 (PB7), R310.2, U403.23 (SDA)
SDA2: J402.4, U401.4 (SD0)
SDA3: J406.4, U401.6 (SD1)
SDA3_MCU: IC302.99 (PC9), J304.3, R312.2
SDA4: J409.4, U401.8 (SD2)
SDA4_MCU: IC302.55 (PF15), R315.2, U401.23 (SDA)
SDA5: J413.4, U401.10 (SD3)
SDA6: J410.4, U401.15 (SD5)
SDA7: J414.4, U401.13 (SD4)
SDA8: J403.4, U403.6 (SD1)
SDA9: J407.4, U403.4 (SD0)
SDA10: J404.4, U403.19 (SD7)
SDA11: J408.4, U403.17 (SD6)
SDA12: J411.4, U403.15 (SD5)
SDA13: J415.4, U403.10 (SD3)
SDA14: J412.4, U403.13 (SD4)
SDA15: J416.4, U403.8 (SD2)
SILENT: IC301.8 (S), IC302.34 (PA0)
SWCLK: IC302.109 (PA14), J301.4 (SWCLK)
SWDIO: IC302.105 (PA13), J301.2 (SWDIO)
SWO: IC302.133 (PB3), J301.6 (SWO)
USB_DN: IC302.103 (PA11), J303.A7 (DN1), J303.B7 (DN2), U302.4 (IO3)
USB_DP: IC302.104 (PA12), J303.A6 (DP1), J303.B6 (DP2), U302.6 (IO4)
VBUS: D304.2 (A), J303.A4_B9 (VBUS), J303.B4_A9 (VBUS), U302.5 (VBUS)
VDDIO1: J401.1, J402.1, J405.1, J406.1, JP401.2 (C)
VDDIO2: J409.1, J410.1, J413.1, J414.1, JP403.2 (C)
VDDIO3: J403.1, J404.1, J407.1, J408.1, JP402.2 (C)
VDDIO4: J411.1, J412.1, J415.1, J416.1, JP404.2 (C)
VIN: C201.1, C202.1, C203.1, C204.1, D201.1 (K), D304.1 (K), IC201.1 (VIN), IC201.5 (EN), IC202.1 (VIN), IC202.5 (EN), Q201.4 (S_1), Q201.7 (S_2)
VIN_RAW: J203.1, Q201.1 (D_1), Q201.2 (D_2), Q201.5 (D_3), Q201.6 (D_4), Q201.8 (D_5)
